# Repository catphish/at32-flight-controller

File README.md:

View this project on [CADLAB.io](https://cadlab.io/project/27011). 

# Open Hardware Flight Controller

Flight contoller based on AT32F435. This project is a work in progress.

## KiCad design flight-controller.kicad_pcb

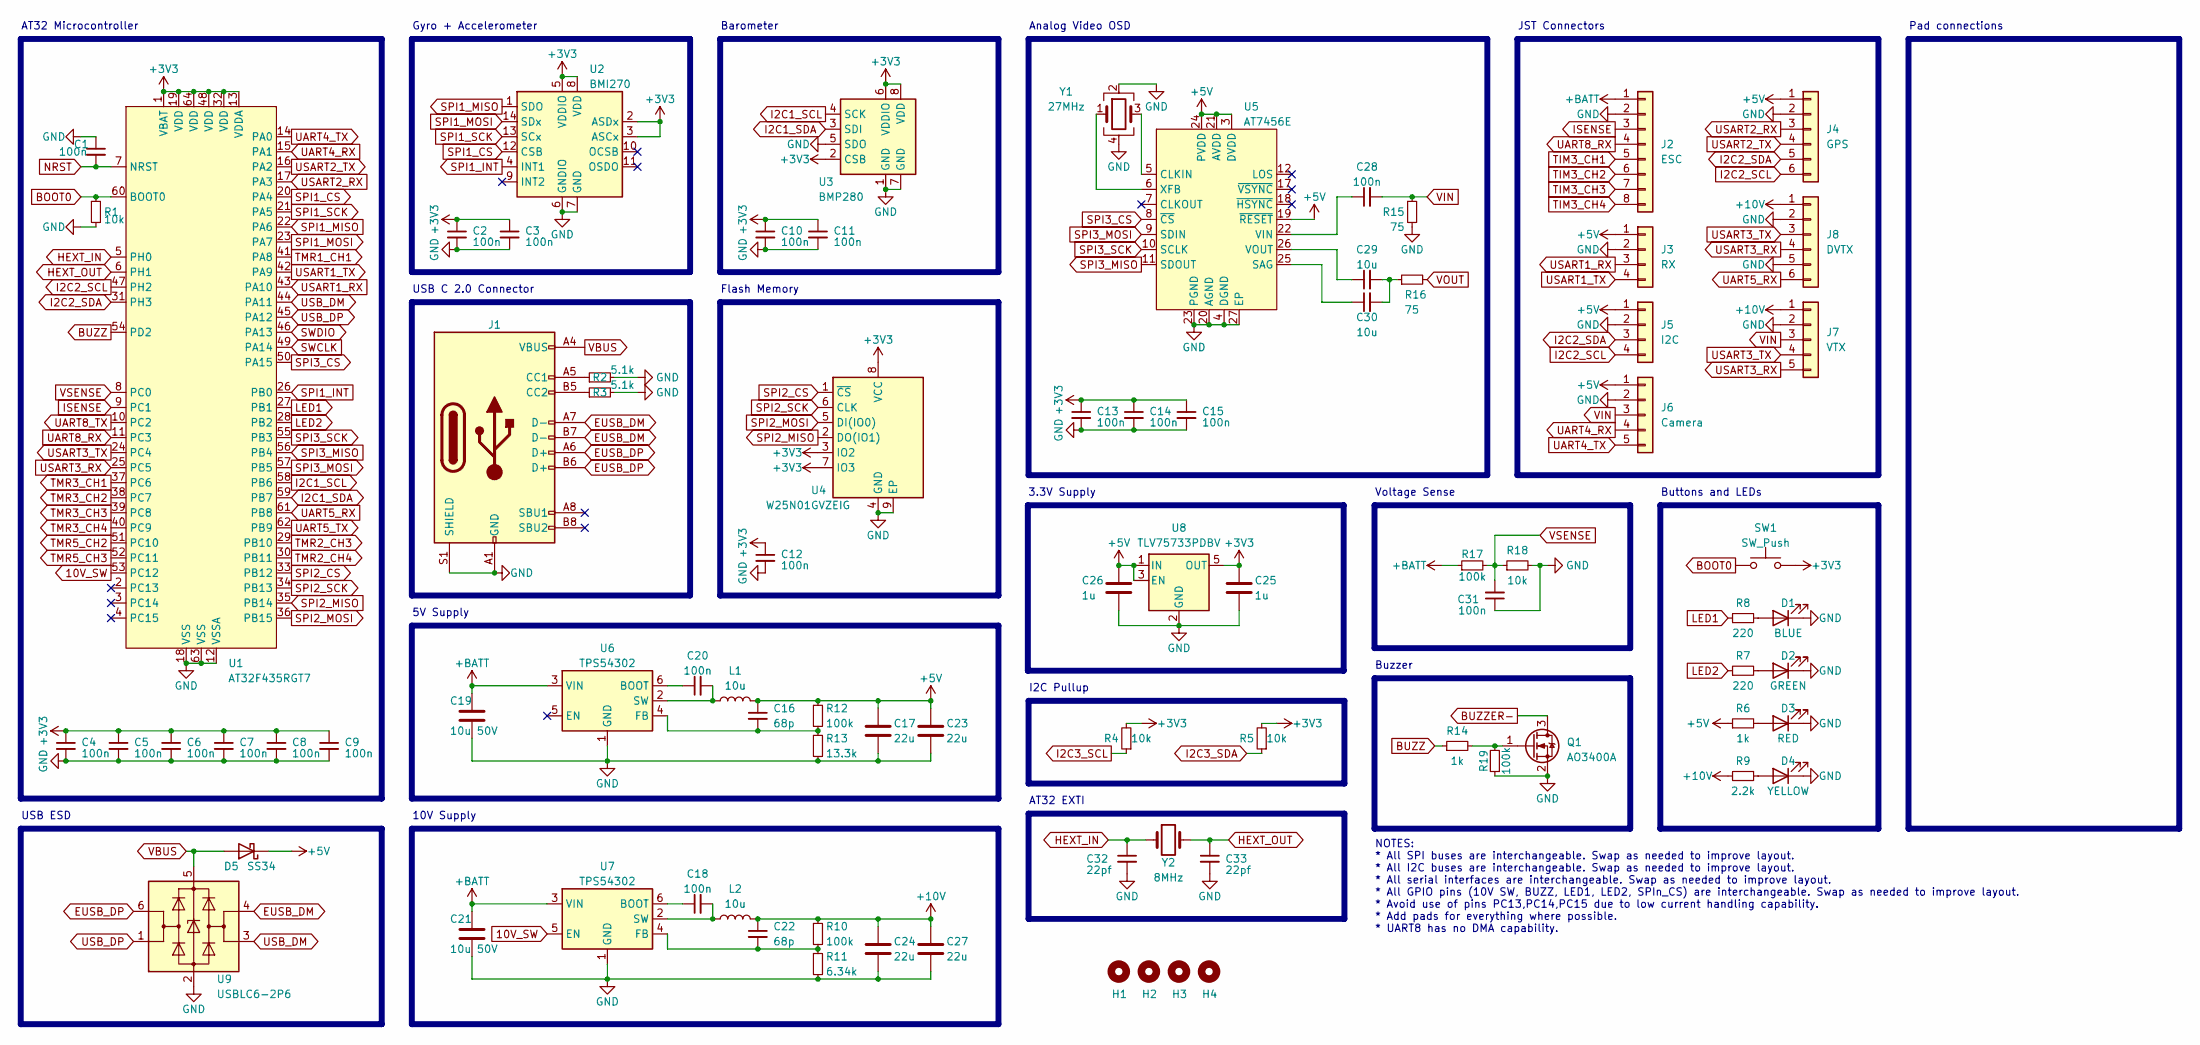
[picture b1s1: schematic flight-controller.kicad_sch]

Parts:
C1, C2, C3, C4, C5, C6, C7, C8, C9, C10, C11, C12, C13, C14, C15, C18, C20, C28, C31: 100n; C_0402_1005Metric; LCSC C1525
C16, C22: 68p; C_0402_1005Metric; LCSC C14441
C17, C23, C24, C27: 22u; C_1206_3216Metric; LCSC C12891
C19, C21: 10u 50V; C_1206_3216Metric; LCSC C13585
C25, C26: 1u; C_0402_1005Metric; LCSC C52923
C29, C30: 10u; C_0603_1608Metric; LCSC C19702
C32, C33: 22pf; C_0402_1005Metric; LCSC C1555
D1: BLUE; LED_0603_1608Metric; LCSC C72041
D2: GREEN; LED_0603_1608Metric; LCSC C72043
D3: RED; LED_0603_1608Metric; LCSC C181863
D4: YELLOW; LED_0603_1608Metric; LCSC C72038
D5: SS34; D_SMA; LCSC C8678
H1, H2, H3, H4: MountingHole; MountingHole_4mm
J1: USB_C_Receptacle_USB2.0; TYPE-C-31-M-12; LCSC C165948
J2: ESC; JST_SH_SM08B-SRSS-TB_1x08-1MP_P1.00mm_Horizontal
J3: RX; JST_SH_SM04B-SRSS-TB_1x04-1MP_P1.00mm_Horizontal
J4: GPS; JST_SH_SM06B-SRSS-TB_1x06-1MP_P1.00mm_Horizontal
J5: I2C; JST_SH_SM04B-SRSS-TB_1x04-1MP_P1.00mm_Horizontal
J6: Camera; JST_SH_SM05B-SRSS-TB_1x05-1MP_P1.00mm_Horizontal
J7: VTX; JST_SH_SM05B-SRSS-TB_1x05-1MP_P1.00mm_Horizontal
J8: DVTX; JST_SH_SM06B-SRSS-TB_1x06-1MP_P1.00mm_Horizontal
L1, L2: 10u; L_Sunlord_MWSA0503S; LCSC C408412
Q1: AO3400A; SOT-23; LCSC C20917
R1, R4, R5, R18: 10k; R_0402_1005Metric; LCSC C25744
R2, R3: 5.1k; R_0402_1005Metric; LCSC C25905
R6: 1k; R_0603_1608Metric; LCSC C21190
R7, R8: 220; R_0603_1608Metric; LCSC C22962
R9: 2.2k; R_0603_1608Metric; LCSC C4190
R10, R12, R17, R19: 100k; R_0402_1005Metric; LCSC C25741
R11: 6.34k; R_0402_1005Metric; LCSC C208926
R13: 13.3k; R_0402_1005Metric; LCSC C310199
R14: 1k; R_0402_1005Metric; LCSC C11702
R15, R16: 75; R_0402_1005Metric; LCSC C25133
SW1: SW_Push; SW_SPST_B3U-1000P; LCSC C231329
U1: AT32F435RGT7; LQFP-64_10x10mm_P0.5mm; LCSC C3029577
U2: BMI270; Bosch_LGA-14_3x2.5mm_P0.5mm; LCSC C2836813
U3: BMP280; Bosch_LGA-8_2x2.5mm_P0.65mm_ClockwisePinNumbering; LCSC C83291
U4: W25N01GVZEIG; WSON-8-1EP_8x6mm_P1.27mm_EP3.4x4.3mm; LCSC C88868
U5: AT7456E; TSSOP-28-1EP_4.4x9.7mm_P0.65mm; LCSC C82351
U6, U7: TPS54302; SOT-23-6; LCSC C311983
U8: TLV75733PDBV; SOT-23-5; LCSC C485517
U9: USBLC6-2P6; SOT-666; LCSC C2827693
Y1: 27MHz; Crystal_SMD_3225-4Pin_3.2x2.5mm; LCSC C9008
Y2: 8MHz; Crystal_SMD_5032-2Pin_5.0x3.2mm; LCSC C115962

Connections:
10V_SW: U1.53 (PC12), U7.5 (EN)
+3V3: C2.1, C3.1, C4.1, C5.1, C6.1, C7.1, C8.1, C9.1, C10.1, C11.1, C12.1, C13.1, C14.1, C15.1, C25.1, R4.2, R5.2, SW1.2, U1.1 (VBAT), U1.13 (VDDA), U1.19 (VDD), U1.32 (VDD), U1.48 (VDD), U1.64 (VDD), U2.2 (ASDx), U2.3 (ASCx), U2.5 (VDDIO), U2.8 (VDD), U3.2 (CSB), U3.6 (VDDIO), U3.8 (VDD), U4.3 (IO2), U4.7 (IO3), U4.8 (VCC), U8.5 (OUT)
+5V: C16.1, C17.1, C23.1, C26.1, D5.1 (K), J3.1, J4.1, J5.1, J6.1, L1.2, R6.1, R12.1, U5.3 (DVDD), U5.19 (~RESET), U5.21 (AVDD), U5.24 (PVDD), U8.1 (IN), U8.3 (EN)
+10V: C22.1, C24.1, C27.1, J7.1, J8.1, L2.2, R9.1, R10.1
+BATT: C19.1, C21.1, J2.1, R17.1, U6.3 (VIN), U7.3 (VIN)
BOOT0: R1.1, SW1.1, U1.60 (BOOT0)
BUZZ: R14.1, U1.54 (PD2)
BUZZER-: Q1.3 (D)
EUSB_DM: J1.A7 (D-), J1.B7 (D-), U9.4 (I/O2)
EUSB_DP: J1.A6 (D+), J1.B6 (D+), U9.6 (I/O1)
GND: C1.1, C2.2, C3.2, C4.2, C5.2, C6.2, C7.2, C8.2, C9.2, C10.2, C11.2, C12.2, C13.2, C14.2, C15.2, C17.2, C19.2, C21.2, C23.2, C24.2, C25.2, C26.2, C27.2, C31.1, C32.2, C33.2, D1.1 (K), D2.1 (K), D3.1 (K), D4.1 (K), J1.A1 (GND), J1.A12 (GND), J1.B1 (GND), J1.B12 (GND), J1.S1 (SHIELD), J2.2, J3.2, J4.2, J5.2, J6.2, J7.2, J8.2, J8.5, Q1.2 (S), R1.2, R2.2, R3.2, R11.2, R13.2, R15.2, R18.2, R19.1, U1.12 (VSSA), U1.18 (VSS), U1.63 (VSS), U2.6 (GNDIO), U2.7 (GND), U3.1 (GND), U3.5 (SDO), U3.7 (GND), U4.4 (GND), U4.9 (EP), U5.4 (DGND), U5.20 (AGND), U5.23 (PGND), U5.27 (EP), U6.1 (GND), U7.1 (GND), U8.2 (GND), U9.2 (GND), Y1.2, Y1.4
HEXT_IN: C32.1, U1.5 (PH0), Y2.1
HEXT_OUT: C33.1, U1.6 (PH1), Y2.2
I2C1_SCL: U1.58 (PB6), U3.4 (SCK)
I2C1_SDA: U1.59 (PB7), U3.3 (SDI)
I2C2_SCL: J4.6, J5.4, U1.47 (PH2)
I2C2_SDA: J4.5, J5.3, U1.31 (PH3)
I2C3_SCL: R4.1
I2C3_SDA: R5.1
ISENSE: J2.3, U1.9 (PC1)
LED1: R8.1, U1.27 (PB1)
LED2: R7.1, U1.28 (PB2)
NRST: C1.2, U1.7 (NRST)
unnamed: C29.2, C30.2, R16.1
unnamed: D1.2 (A), R8.2
unnamed: D2.2 (A), R7.2
unnamed: D3.2 (A), R6.2
unnamed: D4.2 (A), R9.2
unnamed: J1.A5 (CC1), R2.1
unnamed: J1.B5 (CC2), R3.1
unnamed: Q1.1 (G), R14.2, R19.2
unnamed: U5.5 (CLKIN), Y1.3
unnamed: C30.1, U5.25 (SAG)
unnamed: C28.1, U5.22 (VIN)
unnamed: C29.1, U5.26 (VOUT)
unnamed: U5.6 (XFB), Y1.1
unnamed: C20.1, U6.6 (BOOT)
unnamed: C16.2, R12.2, R13.1, U6.4 (FB)
unnamed: C20.2, L1.1, U6.2 (SW)
unnamed: C18.1, U7.6 (BOOT)
unnamed: C22.2, R10.2, R11.1, U7.4 (FB)
unnamed: C18.2, L2.1, U7.2 (SW)
SPI1_CS: U1.20 (PA4), U2.12 (CSB)
SPI1_INT: U1.26 (PB0), U2.4 (INT1)
SPI1_MISO: U1.22 (PA6), U2.1 (SDO)
SPI1_MOSI: U1.23 (PA7), U2.14 (SDx)
SPI1_SCK: U1.21 (PA5), U2.13 (SCx)
SPI2_CS: U1.33 (PB12), U4.1 (~CS)
SPI2_MISO: U1.35 (PB14), U4.2 (DO(IO1))
SPI2_MOSI: U1.36 (PB15), U4.5 (DI(IO0))
SPI2_SCK: U1.34 (PB13), U4.6 (CLK)
SPI3_CS: U1.50 (PA15), U5.8 (~CS)
SPI3_MISO: U1.56 (PB4), U5.11 (SDOUT)
SPI3_MOSI: U1.57 (PB5), U5.9 (SDIN)
SPI3_SCK: U1.55 (PB3), U5.10 (SCLK)
SWCLK: U1.49 (PA14)
SWDIO: U1.46 (PA13)
TIM3_CH1: J2.5
TIM3_CH2: J2.6
TIM3_CH3: J2.7
TIM3_CH4: J2.8
TMR1_CH1: U1.41 (PA8)
TMR2_CH3: U1.29 (PB10)
TMR2_CH4: U1.30 (PB11)
TMR3_CH1: U1.37 (PC6)
TMR3_CH2: U1.38 (PC7)
TMR3_CH3: U1.39 (PC8)
TMR3_CH4: U1.40 (PC9)
TMR5_CH2: U1.51 (PC10)
TMR5_CH3: U1.52 (PC11)
UART4_RX: J6.4, U1.15 (PA1)
UART4_TX: J6.5, U1.14 (PA0)
UART5_RX: J8.6, U1.61 (PB8)
UART5_TX: U1.62 (PB9)
UART8_RX: J2.4, U1.11 (PC3)
UART8_TX: U1.10 (PC2)
USART1_RX: J3.3, U1.43 (PA10)
USART1_TX: J3.4, U1.42 (PA9)
USART2_RX: J4.3, U1.17 (PA3)
USART2_TX: J4.4, U1.16 (PA2)
USART3_RX: J7.5, J8.4, U1.25 (PC5)
USART3_TX: J7.4, J8.3, U1.24 (PC4)
USB_DM: U1.44 (PA11), U9.3 (I/O2)
USB_DP: U1.45 (PA12), U9.1 (I/O1)
VBUS: D5.2 (A), J1.A4 (VBUS), J1.A9 (VBUS), J1.B4 (VBUS), J1.B9 (VBUS), U9.5 (VBUS)
VIN: C28.2, J6.3, J7.3, R15.1
VOUT: R16.2
VSENSE: C31.2, R17.2, R18.1, U1.8 (PC0)

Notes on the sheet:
Voltage Sense
JST Connectors
NOTES: * All SPI buses are interchangeable. Swap as needed to improve layout. * All I2C buses are interchangeable. Swap as needed to improve layout. * All serial interfaces are interchangeable. Swap as needed to improve layout. * All GPIO pins (10V SW, BUZZ, LED1, LED2, SPIn_CS) are interchangeable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
Buzzer
Gyro + Accelerometer
I2C Pullup
10V Supply
5V Supply
AT32 EXTI
Analog Video OSD
AT32 Microcontroller
Barometer
3.3V Supply
USB ESD
Flash Memory
Pad connections
USB C 2.0 Connector
Buttons and LEDs

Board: 4 copper layers, 84 parts (0 on the bottom side), 67 nets, no tracks yet.

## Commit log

2023-05-29 Initial commit. Empty kicad project.
2023-05-30 Add symbols for parts not in kicad library
2023-05-30 Add README
2023-05-30 Begin AT32 pin planning, add USB footprint, schematic basics
2023-05-30 Finish majority of MCU pin mapping
2023-05-30 Update pcb to match minor schematic change
2023-05-31 Tidy up schematic, fix label directions, add decupling caps, pullups, buttons, LEDs
2023-06-01 Add buzzer and power supply designs for consideration
2023-06-02 Backlink to CADLAB.io has been added.
2023-06-02 Add LCSC part numbers for major parts. Provisionally delect power supply capacitors and inductors.
2023-06-02 Add remaining OSD components
2023-06-04 Complete majority of component selection
2023-06-04 Change board to 4-layer
2023-06-04 Assign remaining peripherals to AT32 pins
2023-06-04 Update notes and TODO items
2023-06-04 Add 3D model for USB C, add speculative board and pad shapes
2023-06-05 Add voltage sense divider, rework board shape
2023-06-06 Update schematic PDF
2023-06-06 Add missing HOLD and WP connections to flash
2023-06-06 Add OSD crystal, minor changes to PCB
2023-06-06 Add STEP files for JST connectors
2023-06-06 Add JST connectors
2023-06-07 Add AT32 HSE crystal and choose LED resistors
2023-06-08 Change LED resistors to reduce current, tidy up schematic sheet, changes to AT32 pinout
2023-06-09 Fix LED resistor value
2023-06-09 Change LED resistors again
2023-06-09 Change baro to I2C
2023-06-09 Reduce size of 3v3 regulator capacitors
2023-06-09 Remove unnecessary board layers
2023-06-09 Configure board constraints to match JLCPBC basic 4 layer manufacture
